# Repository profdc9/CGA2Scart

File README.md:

# CGA To SCART

This is a simple CGA to SCART, with an experimental EGA mode to support 640x200 64 color EGA mode.  640x350 mode is not going to work.

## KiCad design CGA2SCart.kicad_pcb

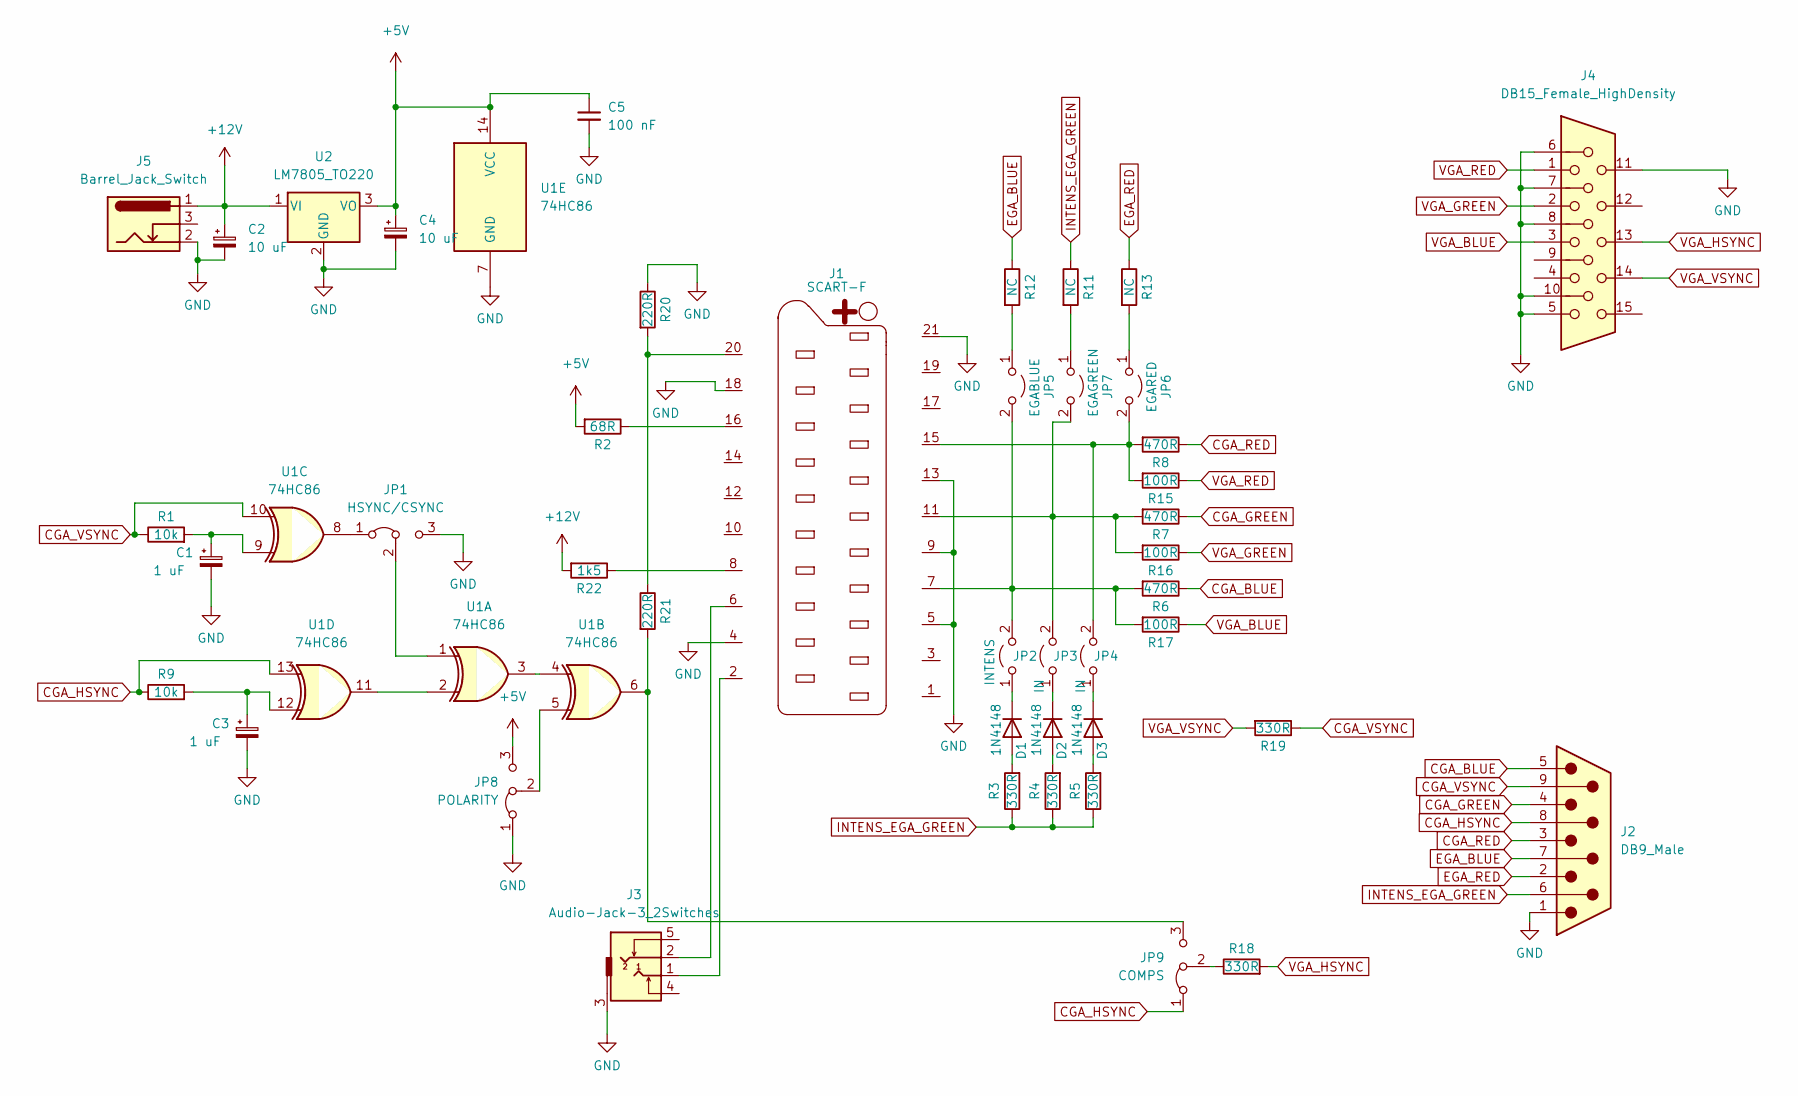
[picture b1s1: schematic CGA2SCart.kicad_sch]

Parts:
C1, C3: 1 uF; CP_Radial_D5.0mm_P2.00mm
C2, C4: 10 uF; CP_Radial_D5.0mm_P2.00mm
C5: 100 nF; C_Disc_D5.0mm_W2.5mm_P5.00mm
D1, D2, D3: 1N4148; D_DO-35_SOD27_P7.62mm_Horizontal
J1: SCART-F; SCART
J2: DB9_Male; DSUB-9_Male_Horizontal_P2.77x2.84mm_EdgePinOffset4.94mm_Hou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
J3: Audio-Jack-3_2Switches; PJ-3240-35mm-stereo
J4: DB15_Female_HighDensity; DSUB-15-HD_Female_Horizontal_P2.29x1.98mm_EdgePinOffset3.03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
J5: Barrel_Jack_Switch; BarrelJack_Horizontal
JP1: HSYNC/CSYNC; PinHeader_1x03_P2.54mm_Vertical
JP2: INTENS; PinHeader_1x02_P2.54mm_Vertical
JP3, JP4: IN; PinHeader_1x02_P2.54mm_Vertical
JP5: EGABLUE; PinHeader_1x02_P2.54mm_Vertical
JP6: EGARED; PinHeader_1x02_P2.54mm_Vertical
JP7: EGAGREEN; PinHeader_1x02_P2.54mm_Vertical
JP8: POLARITY; PinHeader_1x03_P2.54mm_Vertical
JP9: COMPS; PinHeader_1x03_P2.54mm_Vertical
R1, R9: 10k; R_Axial_DIN0207_L6.3mm_D2.5mm_P7.62mm_Horizontal
R2: 68R; R_Axial_DIN0207_L6.3mm_D2.5mm_P7.62mm_Horizontal
R3, R4, R5, R18, R19: 330R; R_Axial_DIN0207_L6.3mm_D2.5mm_P7.62mm_Horizontal
R6, R7, R8: 470R; R_Axial_DIN0207_L6.3mm_D2.5mm_P7.62mm_Horizontal
R11, R12, R13: NC; R_Axial_DIN0207_L6.3mm_D2.5mm_P7.62mm_Horizontal
R15, R16, R17: 100R; R_Axial_DIN0207_L6.3mm_D2.5mm_P7.62mm_Horizontal
R20, R21: 220R; R_Axial_DIN0207_L6.3mm_D2.5mm_P7.62mm_Horizontal
R22: 1k5; R_Axial_DIN0207_L6.3mm_D2.5mm_P7.62mm_Horizontal
U1: 74HC86; DIP-14_W7.62mm_Socket
U2: LM7805_TO220; TO-220-3_Vertical

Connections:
+5V: C4.1, C5.1, JP8.3 (B), R2.2, U1.14 (VCC), U2.3 (VO)
+12V: C2.1, J5.1, R22.2, U2.1 (VI)
CGA_BLUE: J2.5, R6.1
CGA_GREEN: J2.4, R7.1
CGA_HSYNC: J2.8, JP9.1 (A), R9.1, U1.13
CGA_RED: J2.3, R8.1
CGA_VSYNC: J2.9, R1.1, R19.1, U1.10
EGA_BLUE: J2.7, R12.1
EGA_RED: J2.2, R13.1
GND: C1.2, C2.2, C3.2, C4.2, C5.2, J1.4, J1.5, J1.9, J1.13, J1.18, J1.21, J2.1, J3.3, J4.5, J4.6, J4.7, J4.8, J4.10, J4.11, J5.2, JP1.3 (B), JP8.1 (A), R20.1, U1.7 (GND), U2.2 (GND)
INTENS_EGA_GREEN: J2.6, R3.1, R4.1, R5.1, R11.1
unnamed: C1.1, R1.2, U1.9
unnamed: C3.1, R9.2, U1.12
unnamed: D1.1 (K), JP2.1 (A)
unnamed: D1.2 (A), R3.2
unnamed: D2.1 (K), JP3.1 (A)
unnamed: D2.2 (A), R4.2
unnamed: D3.1 (K), JP4.1 (A)
unnamed: D3.2 (A), R5.2
unnamed: J1.2, J3.1
unnamed: J1.6, J3.2
unnamed: J1.7, JP2.2 (B), JP5.2 (B), R6.2, R17.2
unnamed: J1.8, R22.1
unnamed: J1.11, JP3.2 (B), JP7.2 (B), R7.2, R16.2
unnamed: J1.15, JP4.2 (B), JP6.2 (B), R8.2, R15.2
unnamed: J1.16, R2.1
unnamed: J1.20, R20.2, R21.1
unnamed: JP1.1 (A), U1.8
unnamed: JP1.2 (C), U1.1
unnamed: JP5.1 (A), R12.2
unnamed: JP6.1 (A), R13.2
unnamed: JP7.1 (A), R11.2
unnamed: JP8.2 (C), U1.5
unnamed: JP9.2 (C), R18.1
unnamed: JP9.3 (B), R21.2, U1.6
unnamed: U1.3, U1.4
unnamed: U1.2, U1.11
VGA_BLUE: J4.3, R17.1
VGA_GREEN: J4.2, R16.1
VGA_HSYNC: J4.13, R18.2
VGA_RED: J4.1, R15.1
VGA_VSYNC: J4.14, R19.2

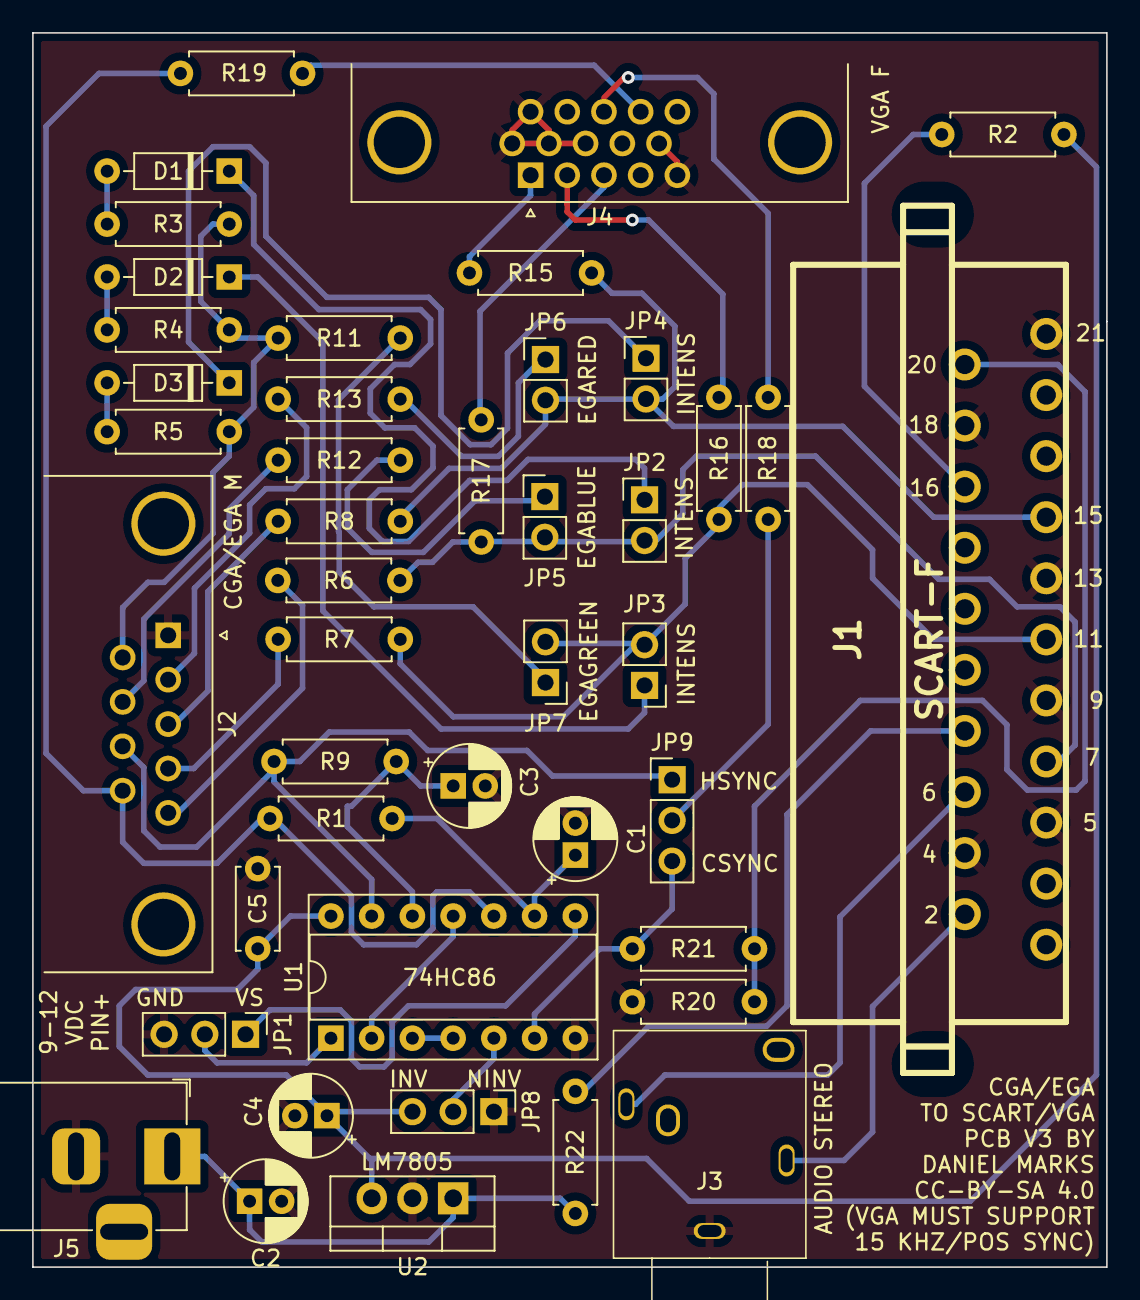
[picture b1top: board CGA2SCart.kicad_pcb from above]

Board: 2 copper layers, 67.0 x 77.0 mm, 44 parts (0 on the bottom side), 42 nets.

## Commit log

2022-09-11 Trying a different README
2022-09-11 Fix filename
2022-09-11 Corrected sync problem
2022-09-11 Added a VGA port
2022-10-22 Put SCART connector on the right way...
2022-11-12 Fixed problem with VGA pins...
2022-11-13 Other connections fixed
2022-12-05 V3 of CGA2SCART, change CSYNC to XOR presync
2022-12-12 Fixed stupid double XOR thing, why can't I get this right?
2022-12-22 Added CSYNC to VGA option

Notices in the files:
CGA2SCart.kicad_pcb:
CC-BY-SA 4.0
